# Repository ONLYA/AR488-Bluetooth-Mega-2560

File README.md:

View this project on [CADLAB.io](https://cadlab.io/project/26454). 

# AR488 Bluetooth Mega 2560
 Source code and KiCad PCB design files for AR488 with Arduino Mega 2560

This board is capable to communicate IEEE-488 protocol between the instrument and a PC. The communication can be with a USB cable or battery-power Bluetooth communication.
The firmware is from https://github.com/Twilight-Logic/AR488. Thanks to his help for this hardware project.

## Please do not use the previous two releases as they have wrong connection and will make your board not working.
Firmware is in folder `AR488-firmware`. The Schematic and PCB files are edited with KiCad 6. BOM is `AR488-Bluetooth-BOM.csv` (#todo)Gerber Files are compressed in `AR488-Gerber.zip`.

You can find the chips here: [SN75160BN](https://www.mouser.co.uk/ProductDetail/Texas-Instruments/SN75160BN?qs=Dqy2GfToSoSUifmRVz6Aqg%3D%3D) and [SN75161BN](https://www.mouser.co.uk/ProductDetail/Texas-Instruments/SN75161BN?qs=Dqy2GfToSoS%252BO4WL2FUX5A%3D%3D).

The GPIB connector I use: [112-024-213R001](https://www.mouser.co.uk/ProductDetail/NorComp/112-024-213R001?qs=IGgAdOvCTsR9oVdHJ26vTQ%3D%3D). Please note that this is a *female* connector, so you will need a GPIB male-male cable.

The Level Shifter (U3) was purchased from [here](https://www.amazon.co.uk/gp/product/B082F6BSB5/ref=ppx_yo_dt_b_asin_title_o09_s00?ie=UTF8&psc=1). It is currently out of stock. However, there are a lot of similar devices. I believed you can easily find an alternative.
The Bluetooth Module (J3) was purchased from [here](https://www.amazon.co.uk/gp/product/B0722MD4FY/ref=ppx_yo_dt_b_asin_title_o02_s00?ie=UTF8&psc=1). When connect it to J2, the attenna track should face upwards.

Connect either JP1 or JP2 to configure whether the DC pin of SN75161BN is connected to REN or Arduino D5. Default should connect JP2. If you want to connect DC-REN, please change that in the `AR488_config.h`.

Connect JP2, "0" side of JP3 and JP4 as the origin setup. You can change that accordingly with the `AR488_config.h`.

## UPDATE 202201311924
1. The connection to the GPIB connector is corrected. Please do not use the previous two releases as they have wrong connection and will make your board not working.
2. A battery circuit is added.
	- (!! DO NOT CONNECT BATTERY IF THE DEVICE IS POWER BY USB OR POWER JACK !!)
	- It accepts voltage range from 3V to 5V. Two AAA batteries are ideal. The SPDT switch will turn on the device.
	- A Boost Switching DC-DC IC (XC9141B50CMR-G)(U4) is used to power the arduino and device.
	- A comparator (U5)(MCP65R41T-1202E/CHY) is used to compare the battery voltage to the 1.21V reference voltage. When the battery voltage drops to the threshold voltage, the "BAT LOW" LED will turn on. The output `CE_OUT` will be driven to LOW.
	- The forward voltage of the "BAT LOW" LED should be less than 2.5V. Red, Amber or Yellow LED will work fine.
	- The potentialmeter is to control the voltage input to the comparator. Adjust it according to the battery specification. To adjust properly, connect a power supply to the `BAT+` input and adjust it to the drained battery voltage. Probe the test point TP1. Adjust RV1 until the voltage is 1.21V.
	- JP5 is the chip enable of the DC-DC IC. If it is connected to BATT, the chip will always be enabled. When connected to OUT, the chip will turn on according to the comparator output `CE_OUT`.

PCB images in KiCad 3D Viewer:

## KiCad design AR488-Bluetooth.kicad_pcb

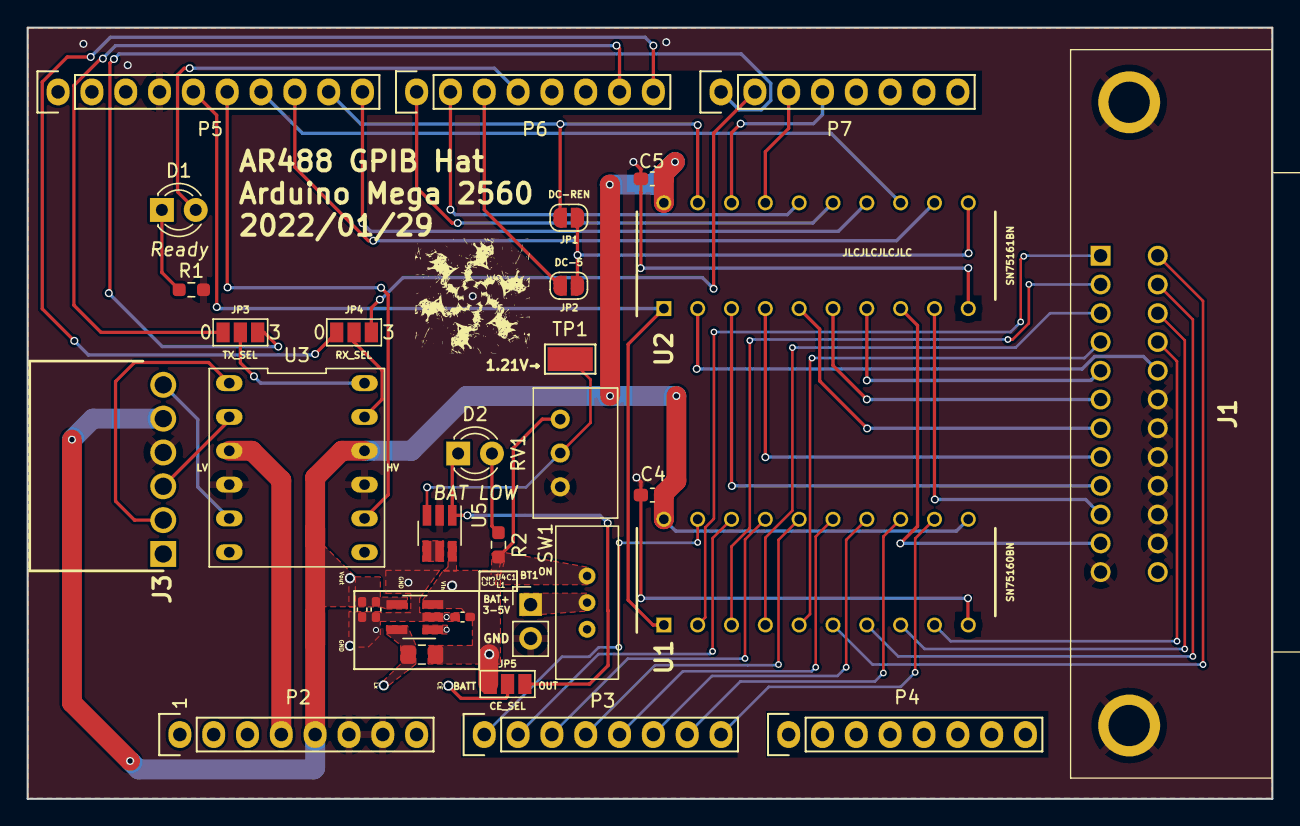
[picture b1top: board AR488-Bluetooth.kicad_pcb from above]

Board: 2 copper layers, 93.5 x 57.9 mm, 32 parts (0 on the bottom side), 58 nets.

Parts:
BT1: Battery; PinHeader_1x02_P2.54mm_Vertical
C1, C2, C3: 10u; C_0402_1005Metric_Pad0.74x0.62mm_HandSolder
C4, C5: 0.1u; C_0603_1608Metric_Pad1.08x0.95mm_HandSolder
D1: Ready; LED_D3.0mm
D2: BAT LOW; LED_D3.0mm
J1: 112-024-213R001; 112024213R001
J3: HC-05; RHDRRA6W79P0X254_1X6_1575X851X241P
JP1: DC-REN; SolderJumper-2_P1.3mm_Open_RoundedPad1.0x1.5mm
JP2: DC-5; SolderJumper-2_P1.3mm_Open_RoundedPad1.0x1.5mm
JP3: TX_SEL; SolderJumper-3_P1.3mm_Open_Pad1.0x1.5mm_NumberLabels
JP4: RX_SEL; SolderJumper-3_P1.3mm_Open_Pad1.0x1.5mm_NumberLabels
JP5: CE_SEL; SolderJumper-3_P1.3mm_Open_Pad1.0x1.5mm_NumberLabels
L1: 4.7u; L_0805_2012Metric_Pad1.15x1.40mm_HandSolder
P2: Power; Socket_Strip_Arduino_1x08
P3, P4: Analog; Socket_Strip_Arduino_1x08
P5: PWM; Socket_Strip_Arduino_1x10
P6: PWM; Socket_Strip_Arduino_1x08
P7: Communication; Socket_Strip_Arduino_1x08
R1, R2: 1k; R_0603_1608Metric_Pad0.98x0.95mm_HandSolder
RV1: 5M; Potentiometer_Bourns_3299W_Vertical
SW1: SW_SPDT; STSSS9121
TP1: TestPoint; TestPoint_Keystone_5015_Micro-Minature
U1: SN75160BN; DIP794W53P254L2540H508Q20N
U2: SN75161BN; DIP794W53P254L2540H508Q20N
U3: Level_Shifter; DIP-12_400_ELL
U4: XC9141B50CMR-G; SOT-23-5_HandSoldering
U5: MCP65R41T-1202E/CHY; SOT-23-6_Handsoldering

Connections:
+3V3: P2.4, U3.3 (LV)
+5V: C2.1, C3.1, C4.1, C5.1, J3.5, P2.5, U1.11 (~PE), U1.20 (VCC), U2.20 (VCC), U3.10 (HV), U4.4 (Vout)
+BATT: C1.1, JP5.1 (A), L1.1, R2.1, RV1.1, SW1.3 (C), U4.3 (BAT), U5.6 (VDD)
/0(Rx0): JP4.1 (A), P6.8
/1(Tx0): JP3.1 (A), P6.7
/4(**): D1.2 (A), P6.4
/5(**): JP2.2 (B), P6.3
/6(**): P6.2, U2.16 (NRFD_2)
/7(**): P6.1, U2.15 (DAV_2)
/8(**): P5.10, U2.14 (EOI_2)
/9(**): JP1.2 (B), P5.9, U2.19 (REN_2)
/10(**): P5.8, U2.12 (SRQ_2)
/11(**): P5.7, U2.13 (ATN_2)
/12(**): P5.6, U3.8 (HV3)
/13(**): P5.5, U1.1 (TE), U2.1 (TE)
/14(Tx3): JP3.3 (B), P7.1
/15(Rx3): JP4.3 (B), P7.2
/16(Tx2): P7.3, U2.17 (NDAC_2)
/17(Rx2): P7.4, U2.18 (IFC_2)
/A0: P3.1, U1.19 (D1)
/A1: P3.2, U1.18 (D2)
/A2: P3.3, U1.17 (D3)
/A3: P3.4, U1.16 (D4)
/A4: P3.5, U1.15 (D5)
/A5: P3.6, U1.14 (D6)
/A6: P3.7, U1.13 (D7)
/A7: P3.8, U1.12 (D8)
/BAT_IN: BT1.1 (+), SW1.2 (B)
/CE: JP5.2 (C), U4.1 (CE)
/CE_OUT: D2.1 (K), JP5.3 (B), U5.1 (OUT)
/EN: J3.6, U3.5 (LV3)
/GPIB1: J1.1 (GPIB1), U1.2 (B1)
/GPIB2: J1.2 (GPIB2), U1.3 (B2)
/GPIB3: J1.3 (GPIB3), U1.4 (B3)
/GPIB4: J1.4 (GPIB4), U1.5 (B4)
/GPIB5: J1.5 (GPIB5), U2.7 (EOI_1)
/GPIB6: J1.6 (GPIB6), U2.6 (DAV_1)
/GPIB7: J1.7 (GPIB7), U2.5 (NRFD_1)
/GPIB8: J1.8 (GPIB8), U2.4 (NDAC_1)
/GPIB9: J1.9 (GPIB9), U2.3 (IFC_1)
/GPIB10: J1.10 (GPIB10), U2.9 (SRQ_1)
/GPIB11: J1.11 (GPIB11), U2.8 (ATN_1)
/GPIB13: J1.13 (GPIB13), U1.6 (B5)
/GPIB14: J1.14 (GPIB14), U1.7 (B6)
/GPIB15: J1.15 (GPIB15), U1.8 (B7)
/GPIB16: J1.16 (GPIB16), U1.9 (B8)
/GPIB17: J1.17 (GPIB17), U2.2 (REN_1)
/IN+: RV1.2, TP1.1, U5.3 (+IN)
/IN-: U5.4 (-IN), U5.5 (Vref)
/Lx: L1.2, U4.5 (Lx)
/RXD: J3.2, U3.1 (LV1)
/TXD: J3.3, U3.2 (LV2)
GND: BT1.2 (-), C1.2, C2.2, C3.2, C4.2, C5.2, J1.12 (GPIB12), J1.18 (GPIB18), J1.19 (GPIB19), J1.20 (GPIB20), J1.21 (GPIB21), J1.22 (GPIB22), J1.23 (GPIB23), J1.MH1, J1.MH2, J3.4, P2.6, P2.7, P5.4, R1.2, RV1.3, U1.10 (GND), U2.10 (GND), U3.4 (LGND), U3.9 (HGND), U4.2 (GND), U5.2 (VSS)
unnamed: D1.1 (K), R1.1
unnamed: D2.2 (A), R2.2
unnamed: JP1.1 (A), JP2.1 (A), U2.11 (DC)
unnamed: JP3.2 (C), U3.12 (HV1)
unnamed: JP4.2 (C), U3.11 (HV2)

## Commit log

2022-01-08 init
2022-01-18 PCB Tune Length
2022-01-19 README update
2022-01-31 Correct the design and add the battery circuit. No Gerber is generated
2022-01-31 Update the images and connect shield to GND
2022-02-14 Update typo in the schematic
2023-01-26 Backlink to CADLAB.io has been added.
